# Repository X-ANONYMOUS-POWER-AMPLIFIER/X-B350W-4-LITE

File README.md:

# X-B350W-4-LITE - SIMPLIFIED MAIN-CIRCUIT MODULE OF 350 WATTS CLASS-B AUDIO POWER AMPLIFIER MAIN-CIRCUIT FOR 4-OHMS OUTPUT LOAD

X-B350W-4-LITE is a power amplifier main-circuit module designed to handle 350 watts of 4-ohms output load power rating. The circuit of X-B350W-4-LITE applies only the effective circuitry models for each of its blocks. Its input-stage applies a minimalist-but-effective LTP (Long Tailed Pair) circuit model, completed with an active-load and an offset null adjustment trimmer. Its VAS (Voltage Amplifier Stage) applies a simple circuit model but with an advanced active-load technique to achieve high amplification performance, with applies only few number of transistors without needing to apply differential-based topology.

## Advanced VAS Model

The VAS of this power amp main-circuit model has an active load that synchronized with the main VAS side to be working as well a fully symmetrical VAS. The output signal from the LTP buffer (Q4006's emitter) copied by a grounded-base transistor amplifier or signal-current-buffer, Q4007, to feed a copy of signal for VAS's loader, Q4008, makes the VAS's loader to be fully actively working side-by-side with the main VAS, Q4009.

The amplification workflow between LTP buffer, Q4006, into the VAS loader, Q4008, isn't for tackling the DC amplification, but limited for tackling AC amplification. The LTP buffer output, Q4006's emitter, is coupled by C4007 into the emitter of Q4007 for gaining the AC signal only, thus Q4007 can keep its main function as a current-source to provide a constant forward-bias-current for Q4008's base and thus Q4008 also kept its function as a current-source for providing the initial constant forward-bias-current for the output-stage while it is also taking function as an active loader of VAS for providing fully symmetrical AC amplification.

There are 3 nodes of NFB lag compensations applied as C4006, C4008, and C4010, to achieve high performance in high frequency amplification (10kHz ~ 15kHz). C4006 compensates the NFB lag for LTP output buffer, Q4006, eliminates non-linear EF buffering. C4008 compensates the NFB lag for high-side VAS, Q4008, eliminates non-linear voltage amplification. C4010 compensates the NFB lag for low-side VAS, Q4009, eliminates non-linear voltage amplification.

By applying this technique, this power amp main-circuit model will be able to achieve wide headroom even for 1-ohms load in fully symmetrically and certainly achieve high performance in nominal output load (4-ohms or 8-ohms). And certainly, one of the important tings is about limit the number of transistors, makes the X-B350W-4-LITE circuit model quit simple with high performance guarantee.

## Warning: None of Current-Limiter Applied Within The Output-Stage

There is none of current-limiter applied within the output-stage, means that it may introduce a risk of short-circuited output. To prevent a fatal output short-circuited overcome, an output protection circuit have to be applied between the X-B350W-4-LITE module's +SPK output and the loudspeaker. The sensing signal of the overload output or output short-circuit can be obtained via CNT4008.

You may have a question, why none of current-limiter applied within the output-stage? The answer is: Applying the current-limiters within the output-stage, as it commonly applied "just to drop the signal amplitude of the output-stage driver transistor bases" - is not really effective since the VAS will always maintain its signal-current along to follow its amplification level although the current-limiter actives as it detects a short-circuited output.

## License

1. **License Grant**  
The Licensor hereby grants you a worldwide, royalty-free, non-exclusive, perpetual license to use the circuit design for the non-commercial purposes only.
2. **Conditions**  
Attribution: You must provide credit to the original creator when distributing this circuit design.
3. **Disclaimer of Warranty**  
THE DESIGN IS PROVIDED "AS IS". THE LICENSOR MAKES NO WARRANTIES, EXPRESS OR IMPLIED, REGARDING THE DESIGN, INCLUDING BUT NOT LIMITED TO ANY IMPLIED WARRANTIES OF MERCHANTABILITY OR FITNESS FOR A PARTICULAR PURPOSE.
4. **Limitation of Liability**  
IN NO EVENT SHALL THE LICENSOR BE LIABLE FOR ANY DAMAGES, INCLUDING BUT NOT LIMITED TO DIRECT, INDIRECT, INCIDENTAL, OR CONSEQUENTIAL DAMAGES ARISING OUT OF THE USE OF THE DESIGN.

# Design Files Bundle Download

Design files bundle is available for download by follow the URL: [https://github.com/X-ANONYMOUS-POWER-AMPLIFIER/X-B350W-4-LITE/archive/refs/heads/main.zip](https://github.com/X-ANONYMOUS-POWER-AMPLIFIER/X-B350W-4-LITE/archive/refs/heads/main.zip)

The main design files of schematic and PCB design are in [KiCad](https://www.kicad.org/) V.9.x format.

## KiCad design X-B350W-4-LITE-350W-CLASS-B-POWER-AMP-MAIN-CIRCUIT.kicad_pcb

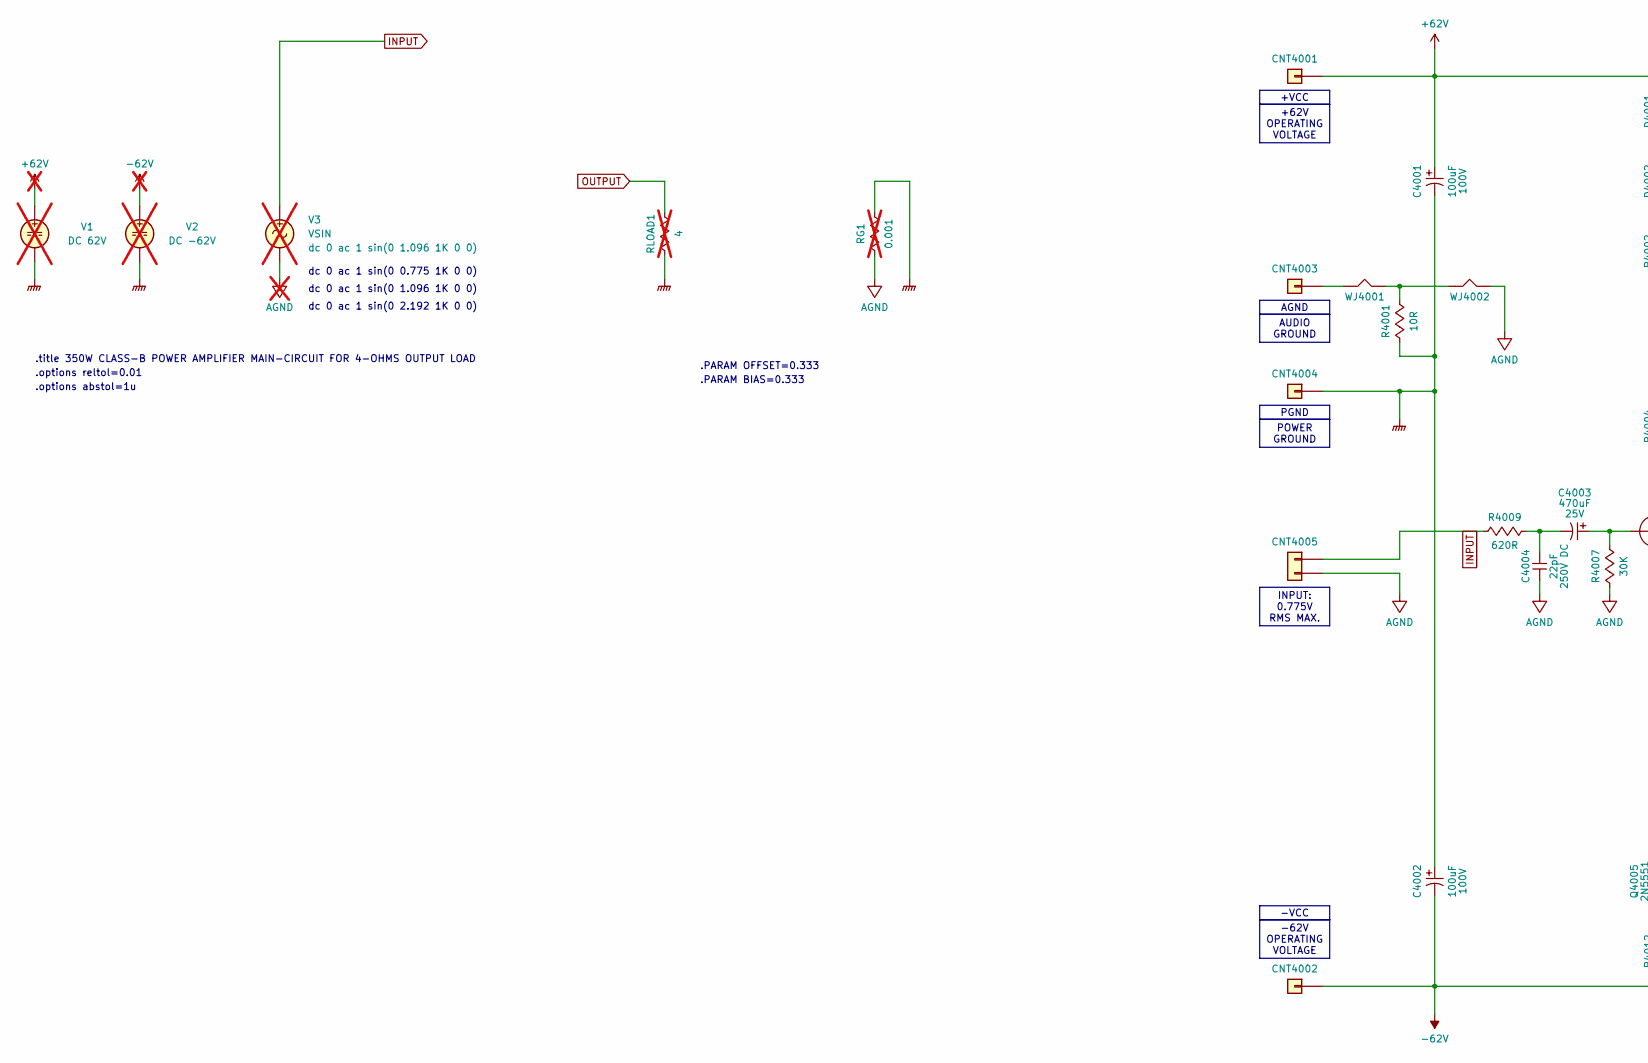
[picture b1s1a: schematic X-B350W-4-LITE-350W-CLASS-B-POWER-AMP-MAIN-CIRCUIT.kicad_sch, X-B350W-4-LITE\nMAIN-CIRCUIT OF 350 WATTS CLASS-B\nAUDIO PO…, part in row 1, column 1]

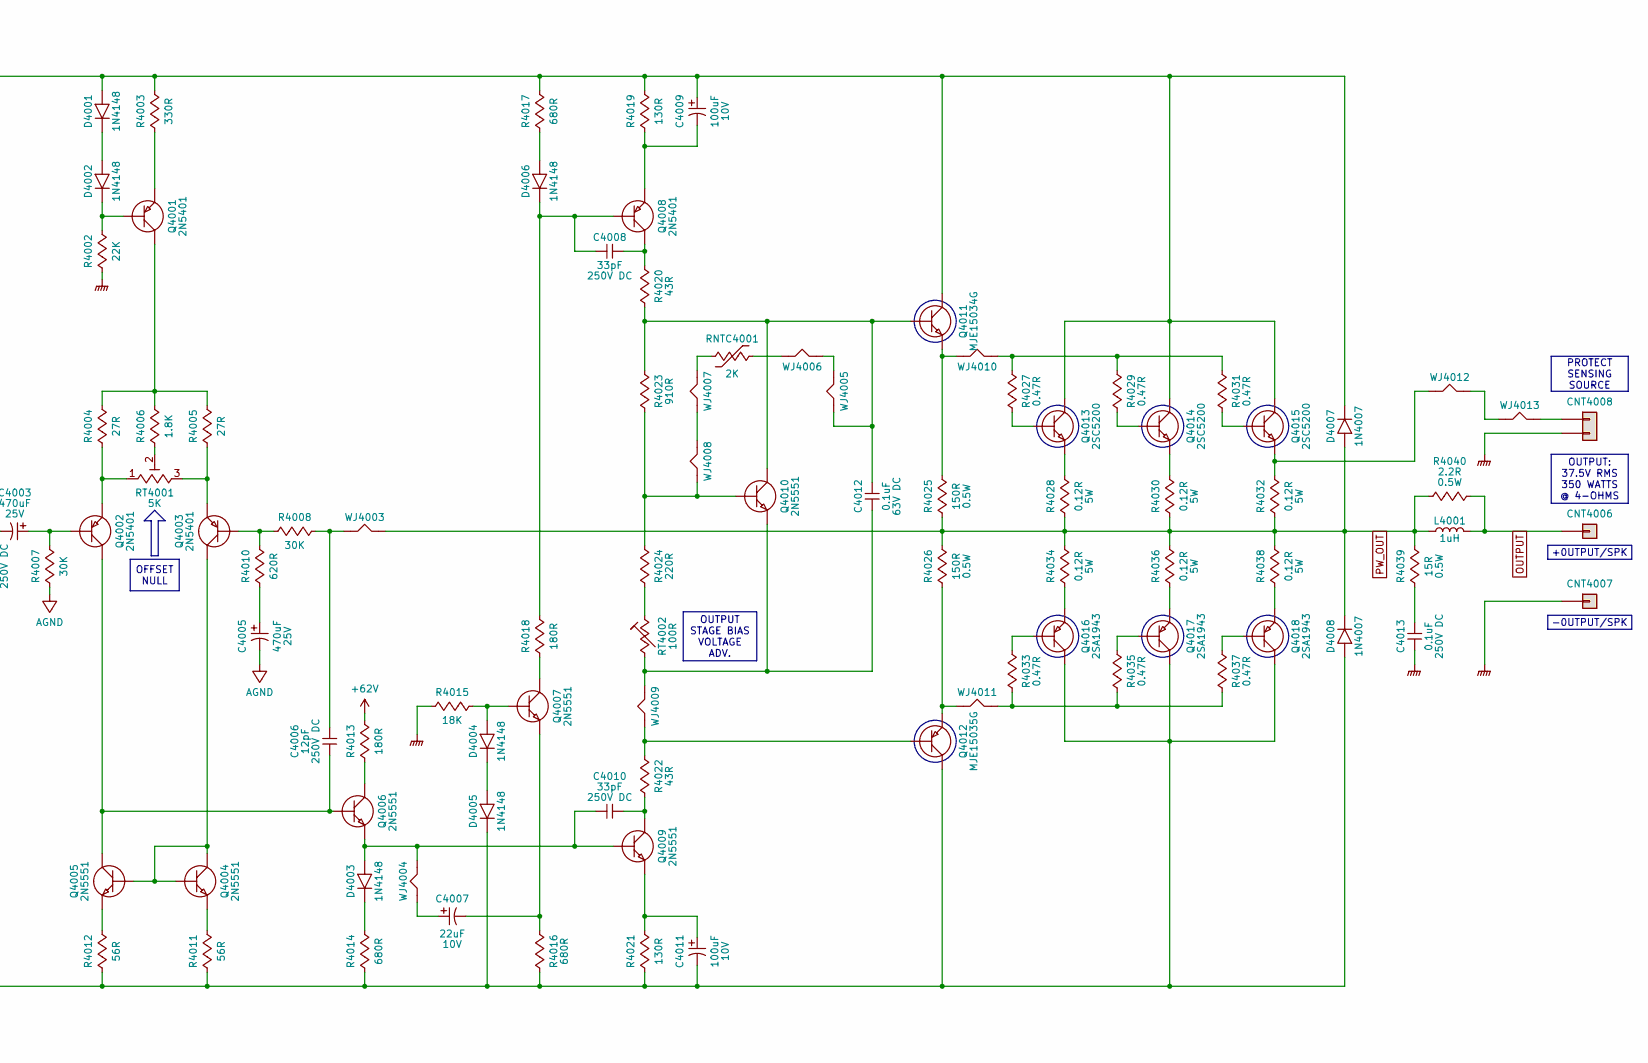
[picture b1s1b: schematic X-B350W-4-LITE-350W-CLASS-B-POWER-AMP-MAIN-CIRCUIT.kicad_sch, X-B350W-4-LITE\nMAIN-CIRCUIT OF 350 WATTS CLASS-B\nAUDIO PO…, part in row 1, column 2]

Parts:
C4001, C4002: 100uF; CP_Radial_D10.0mm_P5.00mm; Rating 100V
C4003, C4005: 470uF; CP_Radial_D8.0mm_P4.00mm_P5.00mm; Rating 25V
C4004: 22pF; C_Disc_D7.5mm_W2.5mm_P5.08mm; Rating 250V DC
C4006: 12pF; C_Disc_D7.5mm_W2.5mm_P5.08mm; Rating 250V DC
C4007: 22uF; CP_Radial_D6.3mm_P2.50mm; Rating 10V
C4008, C4010: 33pF; C_Disc_D7.5mm_W2.5mm_P5.08mm; Rating 250V DC
C4009, C4011: 100uF; CP_Radial_D6.3mm_P2.50mm; Rating 10V
C4012: 0.1uF; C_Rect_L7.5mm_W2.5mm_P5.00mm_WIMA_MKS2; Rating 63V DC
C4013: 0.1uF; C_Rect_L7.2mm_W4.5mm_P5.00mm_FKS2_FKP2_MKS2_MKP2; Rating 250V DC
CNT4001, CNT4002, CNT4003, CNT4004, CNT4006, CNT4007: 2376582-2; PCB_TAB_250_FASTON_TPBR
CNT4005, CNT4008: 22-27-2021; Molex_KK-254_AE-6410-02A_1x02_P2.54mm_Vertical
D4001, D4002, D4003, D4004, D4005, D4006: 1N4148; D_DO-35_SOD27_P10.16mm_Horizontal
D4007, D4008: 1N4007; D_DO-41_SOD81_P10.16mm_Horizontal
L4001: 1uH; Inductor_Air_Core_1uH
Q4001, Q4002, Q4003, Q4008: 2N5401; TO-92_3_Wide
Q4004, Q4005, Q4006, Q4007, Q4009, Q4010: 2N5551; TO-92_3_Wide
Q4011: MJE15034G; TO-220-3_Vertical_With_Small_Heatsink
Q4012: MJE15035G; TO-220-3_Vertical_With_Small_Heatsink
Q4013, Q4014, Q4015: 2SC5200; TO-264-3_Vertical
Q4016, Q4017, Q4018: 2SA1943; TO-264-3_Vertical
R4001: 10R; R_Axial_DIN0207_L6.3mm_D2.5mm_P10.16mm; Rating 0.25W
R4002: 22K; R_Axial_DIN0207_L6.3mm_D2.5mm_P10.16mm; Rating 0.25W
R4003: 330R; R_Axial_DIN0207_L6.3mm_D2.5mm_P10.16mm; Rating 0.25W
R4004, R4005: 27R; R_Axial_DIN0207_L6.3mm_D2.5mm_P10.16mm; Rating 0.25W
R4006: 1.8K; R_Axial_DIN0207_L6.3mm_D2.5mm_P10.16mm; Rating 0.25W
R4007, R4008: 30K; R_Axial_DIN0207_L6.3mm_D2.5mm_P10.16mm; Rating 0.25W
R4009, R4010: 620R; R_Axial_DIN0207_L6.3mm_D2.5mm_P10.16mm; Rating 0.25W
R4011, R4012: 56R; R_Axial_DIN0207_L6.3mm_D2.5mm_P10.16mm; Rating 0.25W
R4013, R4018: 180R; R_Axial_DIN0207_L6.3mm_D2.5mm_P10.16mm; Rating 0.25W
R4014, R4016, R4017: 680R; R_Axial_DIN0207_L6.3mm_D2.5mm_P10.16mm; Rating 0.25W
R4015: 18K; R_Axial_DIN0207_L6.3mm_D2.5mm_P10.16mm; Rating 0.25W
R4019, R4021: 130R; R_Axial_DIN0207_L6.3mm_D2.5mm_P10.16mm; Rating 0.25W
R4020, R4022: 43R; R_Axial_DIN0207_L6.3mm_D2.5mm_P10.16mm; Rating 0.25W
R4023: 910R; R_Axial_DIN0207_L6.3mm_D2.5mm_P10.16mm; Rating 0.25W
R4024: 220R; R_Axial_DIN0207_L6.3mm_D2.5mm_P10.16mm; Rating 0.25W
R4025, R4026: 150R; R_Axial_DIN0309_L9.0mm_D3.2mm_P12.70mm; Rating 0.5W
R4027, R4029, R4031, R4033, R4035, R4037: 0.47R; R_Axial_DIN0207_L6.3mm_D2.5mm_P10.16mm; Rating 0.25W
R4028, R4030, R4032, R4034, R4036, R4038: 0.12R; R_BPR_5W; Rating 5W
R4039: 15R; R_Axial_DIN0309_L9.0mm_D3.2mm_P12.70mm; Rating 0.5W
R4040: 2.2R; R_Axial_DIN0309_L9.0mm_D3.2mm_P12.70mm; Rating 0.5W
RG1: 0.001; R_Axial_DIN0207_L6.3mm_D2.5mm_P10.16mm; Rating 0.25W; not fitted
RLOAD1: 4; R_Axial_DIN0207_L6.3mm_D2.5mm_P10.16mm; Rating 0.25W; not fitted
RNTC4001: 2K; NTC_D5.0mm_T2.5mm_SP2.50mm_Flip_Mount
RT4001: 5K; Potentiometer_Bourns_3296W_Vertical
RT4002: 100R; Potentiometer_Bourns_3296W_Vertical
V1: DC 62V; not fitted
V2: DC -62V; not fitted
V3: VSIN; not fitted
WJ4001, WJ4002, WJ4003, WJ4005, WJ4008, WJ4013: Wire Jumper; J_10.16mm
WJ4004, WJ4006, WJ4007, WJ4009, WJ4010, WJ4011, WJ4012: Wire Jumper; J_12.7mm

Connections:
0: C4001.2, C4002.1, C4013.2, CNT4004.1, CNT4007.1, CNT4008.2, R4001.1, R4002.2, R4015.1, RG1.1, RLOAD1.2, V1.2, V2.2
+62V: C4001.1, C4009.1, CNT4001.1, D4001.2 (A), D4007.1 (K), Q4011.2 (C), Q4013.2 (C), Q4014.2 (C), Q4015.2 (C), R4003.1, R4013.1, R4017.1, R4019.1, V1.1
-62V: C4002.2, C4011.2, CNT4002.1, D4005.1 (K), D4008.2 (A), Q4012.2 (C), Q4016.2 (C), Q4017.2 (C), Q4018.2 (C), R4011.2, R4012.2, R4014.2, R4016.2, R4021.2, V2.1
AGND: C4004.2, C4005.2, CNT4005.2, R4007.2, RG1.2, V3.2, WJ4002.2
INPUT: CNT4005.1, R4009.2, V3.1
unnamed: C4003.2, C4004.1, R4009.1
unnamed: C4005.1, R4010.2
unnamed: C4006.1, R4008.1, WJ4003.1
unnamed: C4007.1, WJ4004.1
unnamed: C4013.1, R4039.2
unnamed: CNT4003.1, WJ4001.1
unnamed: CNT4008.1, WJ4013.2
unnamed: D4001.1 (K), D4002.2 (A)
unnamed: D4002.1 (K), Q4001.2 (B), R4002.1
unnamed: C4010.2, D4003.2 (A), Q4006.1 (E), Q4009.2 (B), WJ4004.2
unnamed: D4003.1 (K), R4014.1
unnamed: D4004.2 (A), Q4007.2 (B), R4015.2
unnamed: D4004.1 (K), D4005.2 (A)
unnamed: D4006.2 (A), R4017.2
unnamed: C4008.2, D4006.1 (K), Q4008.2 (B), R4018.1
unnamed: Q4001.3 (C), R4004.1, R4005.1, R4006.1
unnamed: Q4001.1 (E), R4003.2
unnamed: C4003.1, Q4002.2 (B), R4007.1
unnamed: C4006.2, Q4002.3 (C), Q4005.3 (C), Q4006.2 (B)
unnamed: Q4002.1 (E), R4004.2, RT4001.1
unnamed: Q4003.2 (B), R4008.2, R4010.1
unnamed: Q4003.3 (C), Q4004.2 (B), Q4004.3 (C), Q4005.2 (B)
unnamed: Q4003.1 (E), R4005.2, RT4001.3
unnamed: Q4004.1 (E), R4011.1
unnamed: Q4005.1 (E), R4012.1
unnamed: Q4006.3 (C), R4013.2
unnamed: Q4007.3 (C), R4018.2
unnamed: C4007.2, Q4007.1 (E), R4016.1
unnamed: C4008.1, Q4008.3 (C), R4020.1
unnamed: C4009.2, Q4008.1 (E), R4019.2
unnamed: C4010.1, Q4009.3 (C), R4022.2
unnamed: C4011.1, Q4009.1 (E), R4021.1
unnamed: Q4010.2 (B), R4023.2, R4024.1, WJ4008.1
unnamed: C4012.1, Q4010.3 (C), Q4011.1 (B), R4020.2, R4023.1, WJ4005.1
unnamed: C4012.2, Q4010.1 (E), RT4002.2, WJ4009.1
unnamed: Q4011.3 (E), R4025.1, WJ4010.2
unnamed: Q4012.1 (B), R4022.1, WJ4009.2
unnamed: Q4012.3 (E), R4026.2, WJ4011.2
unnamed: Q4013.1 (B), R4027.2
unnamed: Q4013.3 (E), R4028.1
unnamed: Q4014.1 (B), R4029.2
unnamed: Q4014.3 (E), R4030.1
unnamed: Q4015.1 (B), R4031.2
unnamed: Q4015.3 (E), R4032.1, WJ4012.2
unnamed: Q4016.1 (B), R4033.1
unnamed: Q4016.3 (E), R4034.2
unnamed: Q4017.1 (B), R4035.1
unnamed: Q4017.3 (E), R4036.2
unnamed: Q4018.1 (B), R4037.1
unnamed: Q4018.3 (E), R4038.2
unnamed: R4001.2, WJ4001.2, WJ4002.1
unnamed: R4006.2, RT4001.2
unnamed: R4024.2, RT4002.1
unnamed: R4027.1, R4029.1, R4031.1, WJ4010.1
unnamed: R4033.2, R4035.2, R4037.2, WJ4011.1
unnamed: RNTC4001.1, WJ4006.2
unnamed: RNTC4001.2, WJ4007.2
unnamed: WJ4005.2, WJ4006.1
unnamed: WJ4007.1, WJ4008.2
unnamed: WJ4012.1, WJ4013.1
OUTPUT: CNT4006.1, L4001.2, R4040.1, RLOAD1.1
PW_OUT: D4007.2 (A), D4008.1 (K), L4001.1, R4025.2, R4026.1, R4028.2, R4030.2, R4032.2, R4034.1, R4036.1, R4038.1, R4039.1, R4040.2, WJ4003.2

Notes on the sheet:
.options abstol=1u
dc 0 ac 1 sin(0 2.192 1K 0 0)
.options reltol=0.01
.title 350W CLASS-B POWER AMPLIFIER MAIN-CIRCUIT FOR 4-OHMS OUTPUT LOAD
dc 0 ac 1 sin(0 0.775 1K 0 0)
.PARAM BIAS=0.333
.PARAM OFFSET=0.333
dc 0 ac 1 sin(0 1.096 1K 0 0)
PROTECT SENSING SOURCE
-0UTPUT/SPK
-VCC
INPUT: 0.775V RMS MAX.
POWER GROUND
+VCC
+62V OPERATING VOLTAGE
-62V OPERATING VOLTAGE
OUTPUT: 37.5V RMS 350 WATTS @ 4-OHMS
AUDIO GROUND
+0UTPUT/SPK
PGND
OFFSET NULL
AGND
OUTPUT STAGE BIAS VOLTAGE ADV.

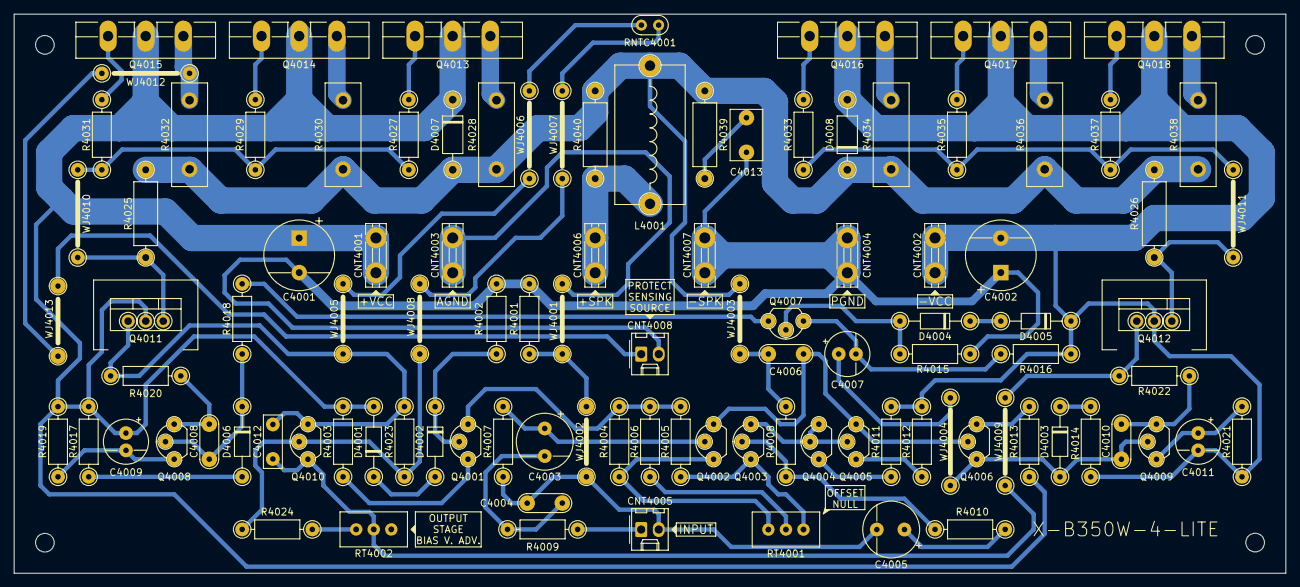
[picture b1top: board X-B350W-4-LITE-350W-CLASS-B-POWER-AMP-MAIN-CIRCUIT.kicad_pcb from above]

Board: 2 copper layers, 184.2 x 81.0 mm, 104 parts (1 on the bottom side), 67 nets.

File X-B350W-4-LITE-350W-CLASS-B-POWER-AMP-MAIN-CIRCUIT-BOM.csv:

"Reference","Value","Rating","Description","MFR Number","Manufacturer","Qty"
"C4001,C4002","100uF","100V","Aluminum Electrolytic Capacitors - Radial Leaded 100uF 100V","ECA-1EM100I ","Panasonic","2"
"C4003,C4005","470uF","25V","Aluminum Electrolytic Capacitors - Radial Leaded 470uF 25V","EEU-FC1E471L","Panasonic","2"
"C4004","22pF","250V DC","Multilayer Ceramic Capacitors MLCC - Leaded 22PF 50V 5% 5.0MM","RDE5C1H220J0K1H03B","Murata","1"
"C4006","12pF","250V DC","Multilayer Ceramic Capacitors MLCC - Leaded 250V 22pF C0G 5% LS=5.08mm","C323C120JAG5TA","KEMET","1"
"C4007","22uF","10V","Aluminum Electrolytic Capacitors - Radial Leaded 10VDC 22uF POLARIZED","ECE-A1AKS220I","Panasonic","1"
"C4008,C4010","33pF","250V DC","Multilayer Ceramic Capacitors MLCC - Leaded 250V 33pF C0G 5% LS=5.08mm","C323C330JAG5TA","KEMET","2"
"C4009,C4011","100uF","10V","Aluminum Electrolytic Capacitors - Radial Leaded 100uF 10V","ECE-A1AKA101","Panasonic","2"
"C4012","0.1uF","63V DC","Film Capacitors 0.1 uF 63 VDC 5%","MKS2C031001A00JI00","WIMA","1"
"C4013","0.1uF","250V DC","Film Capacitors 0.1 uF 250 VDC 20%","MKS2F031001E00MSSD ","WIMA","1"
"CNT4001,CNT4002,CNT4003,CNT4004,CNT4006,CNT4007","2376582-2","","250 FASTON PCB TAB TPBR","2376582-2","TE Connectivity","6"
"CNT4005,CNT4008","22-27-2021","","Headers & Wire Housings 2 POS HEADER","22-27-2021","Molex","2"
"D4001,D4002,D4003,D4004,D4005,D4006","1N4148","","Small Signal Switching Diodes Small Signal Diode, DO-35, 100V, 0.2A, 175C","1N4148","Diotec Semiconductor","6"
"D4007,D4008","1N4007","","Rectifiers Diode, DO-41, 1000V, 1A","1N4007","Diotec Semiconductor","2"
"L4001","1uH","","Air Core Inductor, 16 windings, D = 8 mm, enameled wire diameter = 1.2 mm","","","1"
"Q4001,Q4002,Q4003,Q4008","2N5401","","Bipolar Transistors - BJT PNP 160Vcbo 150Vceo 5.0Vebo 600mA 625mW","2N5401 TIN/LEAD","Central Semiconductor ","4"
"Q4004,Q4005,Q4006,Q4007,Q4009,Q4010","2N5551","","Bipolar Transistors - BJT NPN 180Vcbo 160Vceo 6.0Vebo 600mA 625mW\","2N5551 TIN/LEAD","Central Semiconductor ","6"
"Q4011","MJE15034G","","Bipolar Transistors - BJT 4A 350V 50W NPN","MJE15034G","onsemi","1"
"Q4012","MJE15035G","","Bipolar Transistors - BJT 4A 350V 50W PNP","MJE15035G","onsemi","1"
"Q4013,Q4014,Q4015","2SC5200","","Bipolar Transistors - BJT NPN 230V 15A","2SC5200-O(Q)","Toshiba","3"
"Q4016,Q4017,Q4018","2SA1943","","Bipolar Transistors - BJT PNP 230V 15A","2SA1943-O(Q)","Toshiba","3"
"R4001","10R","0.25W","Metal Film Resistors - Through Hole 10 OHM 1/4W 1%","MFR-25FRE52-10R","YAGEO","1"
"R4002","22K","0.25W","Metal Film Resistors - Through Hole 22K OHM 1/4W 1%","MFR-25FRE52-22K","YAGEO","1"
"R4003","330R","0.25W","Metal Film Resistors - Through Hole 330 OHM 1/4W 1%","MFR-25FRE52-330R","YAGEO","1"
"R4004,R4005","27R","0.25W","Metal Film Resistors - Through Hole 27 OHM 1/4W 1%","MFR-25FRE52-27R","YAGEO","2"
"R4006","1.8K","0.25W","Metal Film Resistors - Through Hole 1.8K OHM 1/4W 1%","MFR-25FRE52-1K8","YAGEO","1"
"R4007,R4008","30K","0.25W","Metal Film Resistors - Through Hole 30K OHM 1/4W 1%","MFR-25FRE52-30K","YAGEO","2"
"R4009,R4010","620R","0.25W","Metal Film Resistors - Through Hole 620 OHM 1/4W 1%","MFR-25FRE52-620R","YAGEO","2"
"R4011,R4012","56R","0.25W","Metal Film Resistors - Through Hole 56 OHM 1/4W 1%","MFR-25FRE52-56R","YAGEO","2"
"R4013,R4018","180R","0.25W","Metal Film Resistors - Through Hole 180 OHM 1/4W 1%","MFR-25FRE52-180R","YAGEO","2"
"R4014,R4016,R4017","680R","0.25W","Metal Film Resistors - Through Hole 680 OHM 1/4W 1%","MFR-25FRE52-680R","YAGEO","3"
"R4015","18K","0.25W","Metal Film Resistors - Through Hole 18K OHM 1/4W 1%","MFR-25FRE52-18K","YAGEO","1"
"R4019,R4021","130R","0.25W","Metal Film Resistors - Through Hole 100 OHM 1/4W 1%","MFR-25FRE52-100R","YAGEO","2"
"R4020,R4022","43R","0.25W","Metal Film Resistors - Through Hole 680 OHM 1/4W 1%","MFR-25FRE52-680R","YAGEO","2"
"R4023","910R","0.25W","Metal Film Resistors - Through Hole 680 OHM 1/4W 1%","MFR-25FRE52-680R","YAGEO","1"
"R4024","220R","0.25W","Metal Film Resistors - Through Hole 180 OHM 1/4W 1%","MFR-25FRE52-180R","YAGEO","1"
"R4025,R4026","150R","0.5W","Metal Film Resistors - Through Hole 150 OHM 1/5W 1%","MFR-50FTE52-150R","YAGEO","2"
"R4027,R4029,R4031,R4033,R4035,R4037","0.47R","0.25W","Metal Oxide Resistors RSS1/2 .47 5%TR","MOSX1/2CT52RR47J ","KOA Speer","6"
"R4028,R4030,R4032,R4034,R4036,R4038","0.12R","5W","Current Sense Resistors - Through Hole 0.12 Ohm 5W 5% 350ppm","BPR58CR12J","KOA Speer","6"
"R4039","15R","0.5W","Metal Film Resistors - Through Hole 15 OHM 1/5W 1%","MFR-50FTE52-15R","YAGEO","1"
"R4040","2.2R","0.5W","Metal Film Resistors - Through Hole 2.2 OHM 1/5W 1%","MFR-50FTE52-2R2","YAGEO","1"
"RNTC4001","2K","","NTC Thermistors 2Kohm/2% 3528/0.5%","NTCLE100E3202GB0A","Vishay / BC Components","1"
"RT4001","5K","","Trimmer Resistors - Through Hole 3/8"" 5Kohms Sealed Vertical Adjust","3296W-1-502ALF","Bourns","1"
"RT4002","100R","","Trimmer Resistors - Through Hole 3/8"" 100 ohms Sealed Vertical Adjust","3296W-1-101ALF","Bourns","1"
"WJ4001,WJ4002,WJ4003,WJ4004,WJ4005,WJ4006,WJ4007,WJ4008,WJ4009,WJ4010,WJ4011,WJ4012,WJ4013","Wire Jumper","","Wire Jumper","","","13"
